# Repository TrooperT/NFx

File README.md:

NFx
===

Going beyond 2 chips

===

This project is an attempt to extend the highly successful OSHW Nanofury Project to the max.

===

My aim is to create a design that is essentially a modular extension of the NF1. If you have 3 chips, then solder on parts for 3 chips. An additional benefit to this modularity is the ability to tune the voltage to each chip individually to maximize for performance or efficiency.
If you have enough for a full board solder on parts for a full board. The idea is modularity.

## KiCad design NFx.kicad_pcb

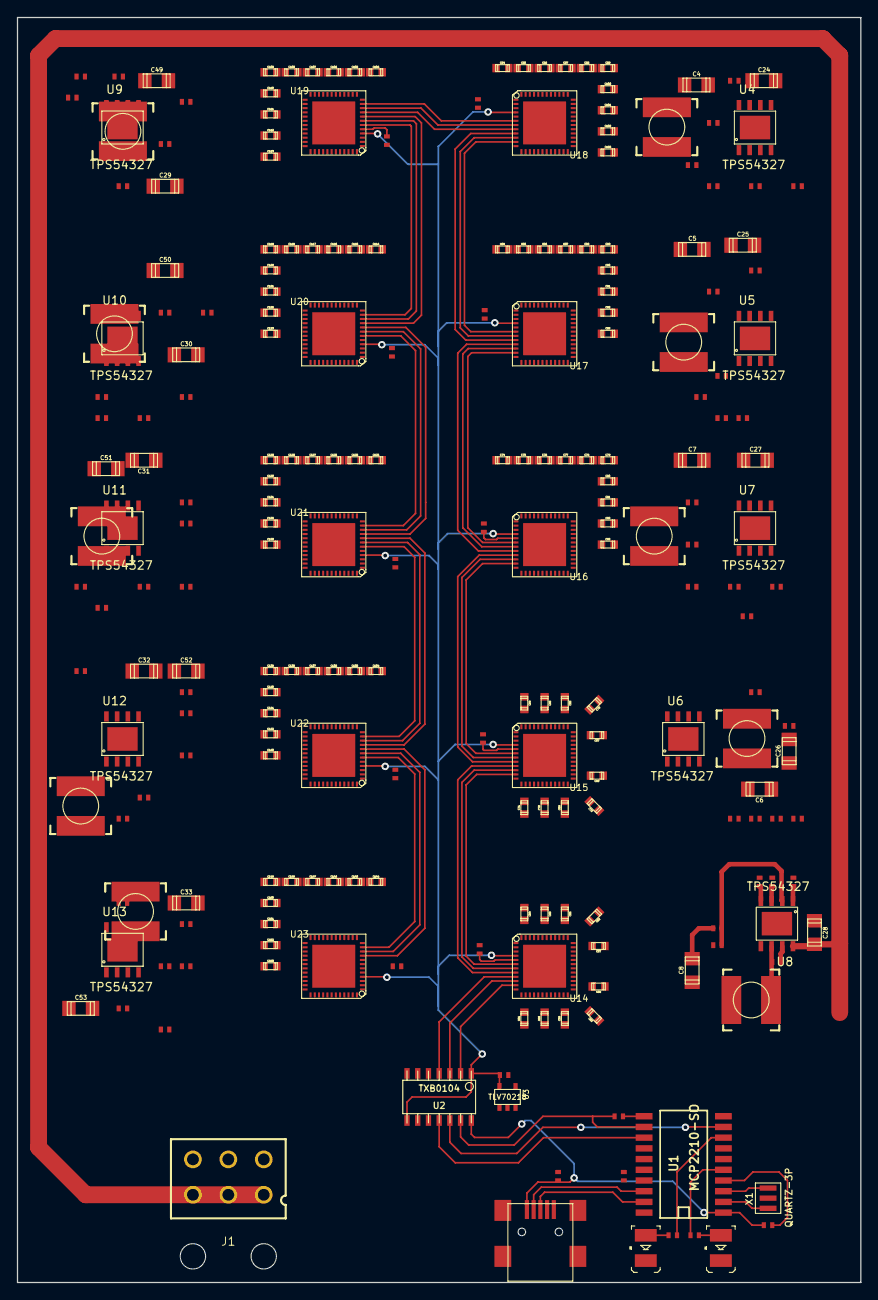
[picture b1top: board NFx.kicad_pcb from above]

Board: 2 copper layers, 100.0 x 150.0 mm, 235 parts (0 on the bottom side), 129 nets.

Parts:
C1: 0.1uF; 0402
C2: 4.7uF; 0402
C3: 4.7UF; 0402
C4, C5, C6, C7, C8, C49, C50, C51, C52, C53: 47UF; c_1206
C9, C10, C11, C12, C13, C44, C45, C46, C47, C48: 0.1UF; 0402
C14, C15, C16, C17, C19, C36, C38, C41, C42, C43: 1.0UF; 0402
C18, C20, C21, C22, C23, C34, C35, C37, C39, C40: 8.2NF; 0402
C24, C25, C26, C27, C28, C29, C30, C31, C32, C33: 22uF; c_1206
C54, C55, C56, C57, C58, C59, C60, C61, C64, C65, C66, C67, C68, C69, C70, C71, C74, C75, C76, C77, C78, C79, C80, C81, C84, C85, C86, C87, C88, C89, C90, C91, C94, C95, C96, C97, C98, C99, C100, C101, C104, C105, C106, C107, C108, C109, C110, C111, C114, C115, C116, C117, C118, C119, C120, C121, C124, C125, C126, C127, C128, C129, C130, C131, C134, C135, C136, C137, C138, C139, C140, C141, C144, C145, C146, C147, C148, C149, C150, C151: 0.1UF; 0603
C62, C63, C72, C73, C82, C83, C92, C93, C102, C103, C112, C113, C122, C123, C132, C133, C142, C143, C152, C153: 22UF; 0603
CN1: MINIUSB; MINIBUSB
D1, D2: LED; 2PLCC
J1: PCIEPWR
L1, L2, L3, L4, L5, L6, L7, L8, L9, L10: 1.5UH; 0630
R1, R2, R3, R4, R35, R36, R37, R38, R39, R40, R41, R42, R43, R44: 1K; 0402
R5, R7, R9, R11, R13, R25, R27, R29, R31, R33: 2.94K; 0402
R6, R8, R10, R12, R14, R26, R28, R30, R32, R34: 22.1K; 0402
R15, R16, R17, R18, R19, R20, R21, R22, R23, R24: 10k; 0402
U1: MCP2210-SO; SOIC20
U2: TXB0104; so-14
U3: TLV70218; SOT23-5
U4, U5, U6, U7, U8, U9, U10, U11, U12, U13: TPS54327; HTSOP-J8
U14, U15, U16, U17, U18, U19, U20, U21, U22, U23: BITFURY; QFN48+1
X1: QUARTZ-3P; CSTCE_G15C

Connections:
0V86A0: C8.2, C54.1, C55.1, C56.1, C57.1, C58.1, C59.1, C60.1, C61.1, C62.1, C63.1, L5.2, R13.2, U14.13, U14.14, U14.15, U14.16, U14.17, U14.18, U14.19, U14.20, U14.21, U14.22, U14.23, U14.24, U14.25, U14.26, U14.27, U14.28, U14.29, U14.30, U14.31, U14.32, U14.33, U14.34, U14.35, U14.36, U14.37, U14.38, U14.39, U14.40, U14.41, U14.42, U14.43, U14.44, U14.45, U14.46, U14.47, U14.48
0V86A1: C6.2, C64.1, C65.1, C66.1, C67.1, C68.1, C69.1, C70.1, C71.1, C72.1, C73.1, L3.2, R9.2, U15.13, U15.14, U15.15, U15.16, U15.17, U15.18, U15.19, U15.20, U15.21, U15.22, U15.23, U15.24, U15.25, U15.26, U15.27, U15.28, U15.29, U15.30, U15.31, U15.32, U15.33, U15.34, U15.35, U15.36, U15.37, U15.38, U15.39, U15.40, U15.41, U15.42, U15.43, U15.44, U15.45, U15.46, U15.47, U15.48
0V86A2: C7.2, C74.1, C75.1, C76.1, C77.1, C78.1, C79.1, C80.1, C81.1, C82.1, C83.1, L4.2, R11.2, U16.13, U16.14, U16.15, U16.16, U16.17, U16.18, U16.19, U16.20, U16.21, U16.22, U16.23, U16.24, U16.25, U16.26, U16.27, U16.28, U16.29, U16.30, U16.31, U16.32, U16.33, U16.34, U16.35, U16.36, U16.37, U16.38, U16.39, U16.40, U16.41, U16.42, U16.43, U16.44, U16.45, U16.46, U16.47, U16.48
0V86A3: C5.2, C84.1, C85.1, C86.1, C87.1, C88.1, C89.1, C90.1, C91.1, C92.1, C93.1, L2.2, R7.2, U17.13, U17.14, U17.15, U17.16, U17.17, U17.18, U17.19, U17.20, U17.21, U17.22, U17.23, U17.24, U17.25, U17.26, U17.27, U17.28, U17.29, U17.30, U17.31, U17.32, U17.33, U17.34, U17.35, U17.36, U17.37, U17.38, U17.39, U17.40, U17.41, U17.42, U17.43, U17.44, U17.45, U17.46, U17.47, U17.48
0V86A4: C4.2, C94.1, C95.1, C96.1, C97.1, C98.1, C99.1, C100.1, C101.1, C102.1, C103.1, L1.2, R5.2, U18.13, U18.14, U18.15, U18.16, U18.17, U18.18, U18.19, U18.20, U18.21, U18.22, U18.23, U18.24, U18.25, U18.26, U18.27, U18.28, U18.29, U18.30, U18.31, U18.32, U18.33, U18.34, U18.35, U18.36, U18.37, U18.38, U18.39, U18.40, U18.41, U18.42, U18.43, U18.44, U18.45, U18.46, U18.47, U18.48
0V86A5: C49.2, C104.1, C105.1, C106.1, C107.1, C108.1, C109.1, C110.1, C111.1, C112.1, C113.1, L6.2, R25.2, U19.13, U19.14, U19.15, U19.16, U19.17, U19.18, U19.19, U19.20, U19.21, U19.22, U19.23, U19.24, U19.25, U19.26, U19.27, U19.28, U19.29, U19.30, U19.31, U19.32, U19.33, U19.34, U19.35, U19.36, U19.37, U19.38, U19.39, U19.40, U19.41, U19.42, U19.43, U19.44, U19.45, U19.46, U19.47, U19.48
0V86A6: C50.2, C114.1, C115.1, C116.1, C117.1, C118.1, C119.1, C120.1, C121.1, C122.1, C123.1, L7.2, R27.2, U20.13, U20.14, U20.15, U20.16, U20.17, U20.18, U20.19, U20.20, U20.21, U20.22, U20.23, U20.24, U20.25, U20.26, U20.27, U20.28, U20.29, U20.30, U20.31, U20.32, U20.33, U20.34, U20.35, U20.36, U20.37, U20.38, U20.39, U20.40, U20.41, U20.42, U20.43, U20.44, U20.45, U20.46, U20.47, U20.48
0V86A7: C51.2, C124.1, C125.1, C126.1, C127.1, C128.1, C129.1, C130.1, C131.1, C132.1, C133.1, L8.2, R29.2, U21.13, U21.14, U21.15, U21.16, U21.17, U21.18, U21.19, U21.20, U21.21, U21.22, U21.23, U21.24, U21.25, U21.26, U21.27, U21.28, U21.29, U21.30, U21.31, U21.32, U21.33, U21.34, U21.35, U21.36, U21.37, U21.38, U21.39, U21.40, U21.41, U21.42, U21.43, U21.44, U21.45, U21.46, U21.47, U21.48
0V86A8: C52.2, C134.1, C135.1, C136.1, C137.1, C138.1, C139.1, C140.1, C141.1, C142.1, C143.1, L9.2, R31.2, U22.13, U22.14, U22.15, U22.16, U22.17, U22.18, U22.19, U22.20, U22.21, U22.22, U22.23, U22.24, U22.25, U22.26, U22.27, U22.28, U22.29, U22.30, U22.31, U22.32, U22.33, U22.34, U22.35, U22.36, U22.37, U22.38, U22.39, U22.40, U22.41, U22.42, U22.43, U22.44, U22.45, U22.46, U22.47, U22.48
0V86A9: C53.2, C144.1, C145.1, C146.1, C147.1, C148.1, C149.1, C150.1, C151.1, C152.1, C153.1, L10.2, R33.2, U23.13, U23.14, U23.15, U23.16, U23.17, U23.18, U23.19, U23.20, U23.21, U23.22, U23.23, U23.24, U23.25, U23.26, U23.27, U23.28, U23.29, U23.30, U23.31, U23.32, U23.33, U23.34, U23.35, U23.36, U23.37, U23.38, U23.39, U23.40, U23.41, U23.42, U23.43, U23.44, U23.45, U23.46, U23.47, U23.48
1V8: C3.2, U2.1, U2.8, U3.5, U14.4, U15.4, U16.4, U17.4, U18.4, U19.4, U20.4, U21.4, U22.4, U23.4
12V0: C24.1, C25.1, C26.1, C27.1, C28.1, C29.1, C30.1, C31.1, C32.1, C33.1, J1.1, J1.2, J1.3, U4.8, U5.8, U6.8, U7.8, U8.8, U9.8, U10.8, U11.8, U12.8, U13.8
GND: C1.2, C2.2, C3.1, C4.1, C5.1, C6.1, C7.1, C8.1, C14.2, C15.2, C16.2, C17.2, C18.2, C19.2, C20.2, C21.2, C22.2, C23.2, C24.2, C25.2, C26.2, C27.2, C28.2, C29.2, C30.2, C31.2, C32.2, C33.2, C34.2, C35.2, C36.2, C37.2, C38.2, C39.2, C40.2, C41.2, C42.2, C43.2, C49.1, C50.1, C51.1, C52.1, C53.1, C54.2, C55.2, C56.2, C57.2, C58.2, C59.2, C60.2, C61.2, C62.2, C63.2, C64.2, C65.2, C66.2, C67.2, C68.2, C69.2, C70.2, C71.2, C72.2, C73.2, C74.2, C75.2, C76.2, C77.2, C78.2, C79.2, C80.2, C81.2, C82.2, C83.2, C84.2, C85.2, C86.2, C87.2, C88.2, C89.2, C90.2, C91.2, C92.2, C93.2, C94.2, C95.2, C96.2, C97.2, C98.2, C99.2, C100.2, C101.2, C102.2, C103.2, C104.2, C105.2, C106.2, C107.2, C108.2, C109.2, C110.2, C111.2, C112.2, C113.2, C114.2, C115.2, C116.2, C117.2, C118.2, C119.2, C120.2, C121.2, C122.2, C123.2, C124.2, C125.2, C126.2, C127.2, C128.2, C129.2, C130.2, C131.2, C132.2, C133.2, C134.2, C135.2, C136.2, C137.2, C138.2, C139.2, C140.2, C141.2, C142.2, C143.2, C144.2, C145.2, C146.2, C147.2, C148.2, C149.2, C150.2, C151.2, C152.2, C153.2, D1.2, D2.2, J1.4, J1.5, J1.6, R6.1, R8.1, R10.1, R12.1, R14.1, R26.1, R28.1, R30.1, R32.1, R34.1, R35.2, R36.2, R37.2, R38.2, R39.2, R40.2, R41.2, R42.2, R43.2, R44.2, U1.20, U2.5, U2.6, U2.7, U2.9, U2.10, U3.2, U3.4, U4.5, U4.9, U5.5, U5.9, U6.5, U6.9, U7.5, U7.9, U8.5, U8.9, U9.5, U9.9, U10.5, U10.9, U11.5, U11.9, U12.5, U12.9, U13.5, U13.9, U14.1, U14.2, U14.3, U14.12, U14.49, U15.1, U15.2, U15.3, U15.12, U15.49, U16.1, U16.2, U16.3, U16.12, U16.49, U17.1, U17.2, U17.3, U17.12, U17.49, U18.1, U18.2, U18.3, U18.12, U18.49, U19.1, U19.2, U19.3, U19.12, U19.49, U20.1, U20.2, U20.3, U20.12, U20.49, U21.1, U21.2, U21.3, U21.12, U21.49, U22.1, U22.2, U22.3, U22.12, U22.49, U23.1, U23.2, U23.3, U23.12, U23.49, X1.2
MISO_1V8_0: U2.4, U14.9
MISO_1V8_1: U14.8, U15.9
MISO_1V8_2: U15.8, U16.9
MISO_1V8_3: U16.8, U17.9
MISO_1V8_4: U17.8, U18.9
MISO_1V8_5: U18.8, U19.9
MISO_1V8_6: U19.8, U20.9
MISO_1V8_7: U20.8, U21.9
MISO_1V8_8: U21.8, U22.9
MISO_1V8_9: U22.8, U23.9
MOSI_1V8_0: U2.3, U14.10
MOSI_1V8_1: U14.7, U15.10
MOSI_1V8_2: U15.7, U16.10
MOSI_1V8_3: U16.7, U17.10
MOSI_1V8_4: U17.7, U18.10
MOSI_1V8_5: U18.7, U19.10
MOSI_1V8_6: U19.7, U20.10
MOSI_1V8_7: U20.7, U21.10
MOSI_1V8_8: U21.7, U22.10
MOSI_1V8_9: U22.7, U23.10
unnamed: CN1.3, U1.19
unnamed: R4.2, U1.12, U2.13
unnamed: U1.9, U2.12
unnamed: U1.13, U2.11
unnamed: R4.1, U1.11
unnamed: D2.1, R2.1
unnamed: R2.2, U1.8
unnamed: R3.1, U1.5
unnamed: D1.1, R3.2
unnamed: U1.2, X1.1
unnamed: U1.3, X1.3
unnamed: R1.1, U1.4
unnamed: C2.1, U1.17
unnamed: CN1.2, U1.18
unnamed: C1.1, CN1.1, R1.2, U1.1, U2.14, U3.1
unnamed: R7.1, R8.2, U5.2
unnamed: C36.1, U9.3
unnamed: C34.1, U9.4
unnamed: R16.1, U5.1
unnamed: C10.1, U5.7
unnamed: C10.2, L2.1, U5.6
unnamed: C38.1, U10.3
unnamed: C35.1, U10.4
unnamed: R21.1, U10.1
unnamed: C45.1, U10.7
unnamed: C45.2, L7.1, U10.6
unnamed: R20.1, U9.1
unnamed: C44.1, U9.7
unnamed: C44.2, L6.1, U9.6
unnamed: R25.1, R26.2, U9.2
unnamed: R17.1, U6.1
unnamed: C11.1, U6.7
unnamed: C11.2, L3.1, U6.6
unnamed: R9.1, R10.2, U6.2
unnamed: C16.1, U6.3
unnamed: C21.1, U6.4
unnamed: C12.2, L4.1, U7.6
unnamed: R11.1, R12.2, U7.2
unnamed: C15.1, U5.3
unnamed: C20.1, U5.4
unnamed: C17.1, U7.3
unnamed: C22.1, U7.4
unnamed: R18.1, U7.1
unnamed: C12.1, U7.7
unnamed: R5.1, R6.2, U4.2
unnamed: C43.1, U13.3
unnamed: C40.1, U13.4
unnamed: C14.1, U4.3
unnamed: C18.1, U4.4
unnamed: R15.1, U4.1
unnamed: C9.1, U4.7
unnamed: C9.2, L1.1, U4.6
unnamed: R33.1, R34.2, U13.2
unnamed: R24.1, U13.1
unnamed: C48.1, U13.7
unnamed: C48.2, L10.1, U13.6
unnamed: R22.1, U11.1
unnamed: C46.1, U11.7
unnamed: C46.2, L8.1, U11.6
unnamed: R27.1, R28.2, U10.2
unnamed: C41.1, U11.3
unnamed: C37.1, U11.4
unnamed: R23.1, U12.1
unnamed: C47.1, U12.7
unnamed: C47.2, L9.1, U12.6
unnamed: R31.1, R32.2, U12.2
unnamed: R29.1, R30.2, U11.2
unnamed: C42.1, U12.3
unnamed: C39.1, U12.4
unnamed: R19.1, U8.1
unnamed: R13.1, R14.2, U8.2
unnamed: C13.1, U8.7
unnamed: C13.2, L5.1, U8.6
unnamed: C23.1, U8.4
unnamed: C19.1, U8.3
unnamed: R36.1, U15.5
unnamed: R35.1, U14.5
unnamed: R37.1, U16.5
unnamed: R38.1, U17.5
unnamed: R39.1, U18.5
unnamed: R41.1, U20.5
unnamed: R40.1, U19.5
unnamed: R44.1, U23.5
unnamed: R42.1, U21.5
unnamed: R43.1, U22.5
SCK_1V8_0: U2.2, U14.11
SCK_1V8_1: U14.6, U15.11
SCK_1V8_2: U15.6, U16.11
SCK_1V8_3: U16.6, U17.11
SCK_1V8_4: U17.6, U18.11
SCK_1V8_5: U18.6, U19.11
SCK_1V8_6: U19.6, U20.11
SCK_1V8_7: U20.6, U21.11
SCK_1V8_8: U21.6, U22.11
SCK_1V8_9: U22.6, U23.11
V_EN: R15.2, R16.2, R17.2, R18.2, R19.2, R20.2, R21.2, R22.2, R23.2, R24.2, U1.14, U3.3

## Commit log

2014-02-19 Initial Commit
    Import docs and lib from NF1
2014-02-20 Push new .lib and .mod files to master
2014-02-21 Finished schematic of VREG subsystem.
    Moved from Rohm BD9C301 to TI TPS54327 to allow main power to be +12V
    and lower min adjustable voltage to 0.76V
2014-02-23 Fill in component values in schematic
2014-02-24 Added ASIC row 0 and added links for power domains and comm lines
    Renumbered components.
    Added LED on MCP2210 GP3 pin to show SPI traffic activity (this feature
    will require either programming of the NFx to modify NVRAM boot
    settings [most likely], or added driver code in mcp init block [less
    likely])
2014-03-08 Fixed schematic wiring mismatch. initial layout and wiring
